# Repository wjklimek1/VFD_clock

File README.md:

# VFD_clock
Clock with VFD display based on STM32 MCU. Displays time, date and temperature.

As a display i used an old VFD tube IW-18 (IV-18). Device displays time (hours, minutes and seconds), date and temperature. Clock is based on STM32F103C8T6 microcontroller and it was programmed with HAL libraries. To boost voltage to required level I used popular SX1308 step-up IC.To power VFD display filament with alternating current i used L293d H-bridge with single transistor serving as simple NOT gate.

Schematic and PCB were designed using KiCad. You can find schematic in PDF format in PDFs folder of this repository.

Sensors used in the project:
RTC - DS3231 I2C real time clock

DS18B20 - 1-Wire temperature sensor (not utilized in software yet)
DHT11   - digital relative humidity sensor (not utilized in software yet)

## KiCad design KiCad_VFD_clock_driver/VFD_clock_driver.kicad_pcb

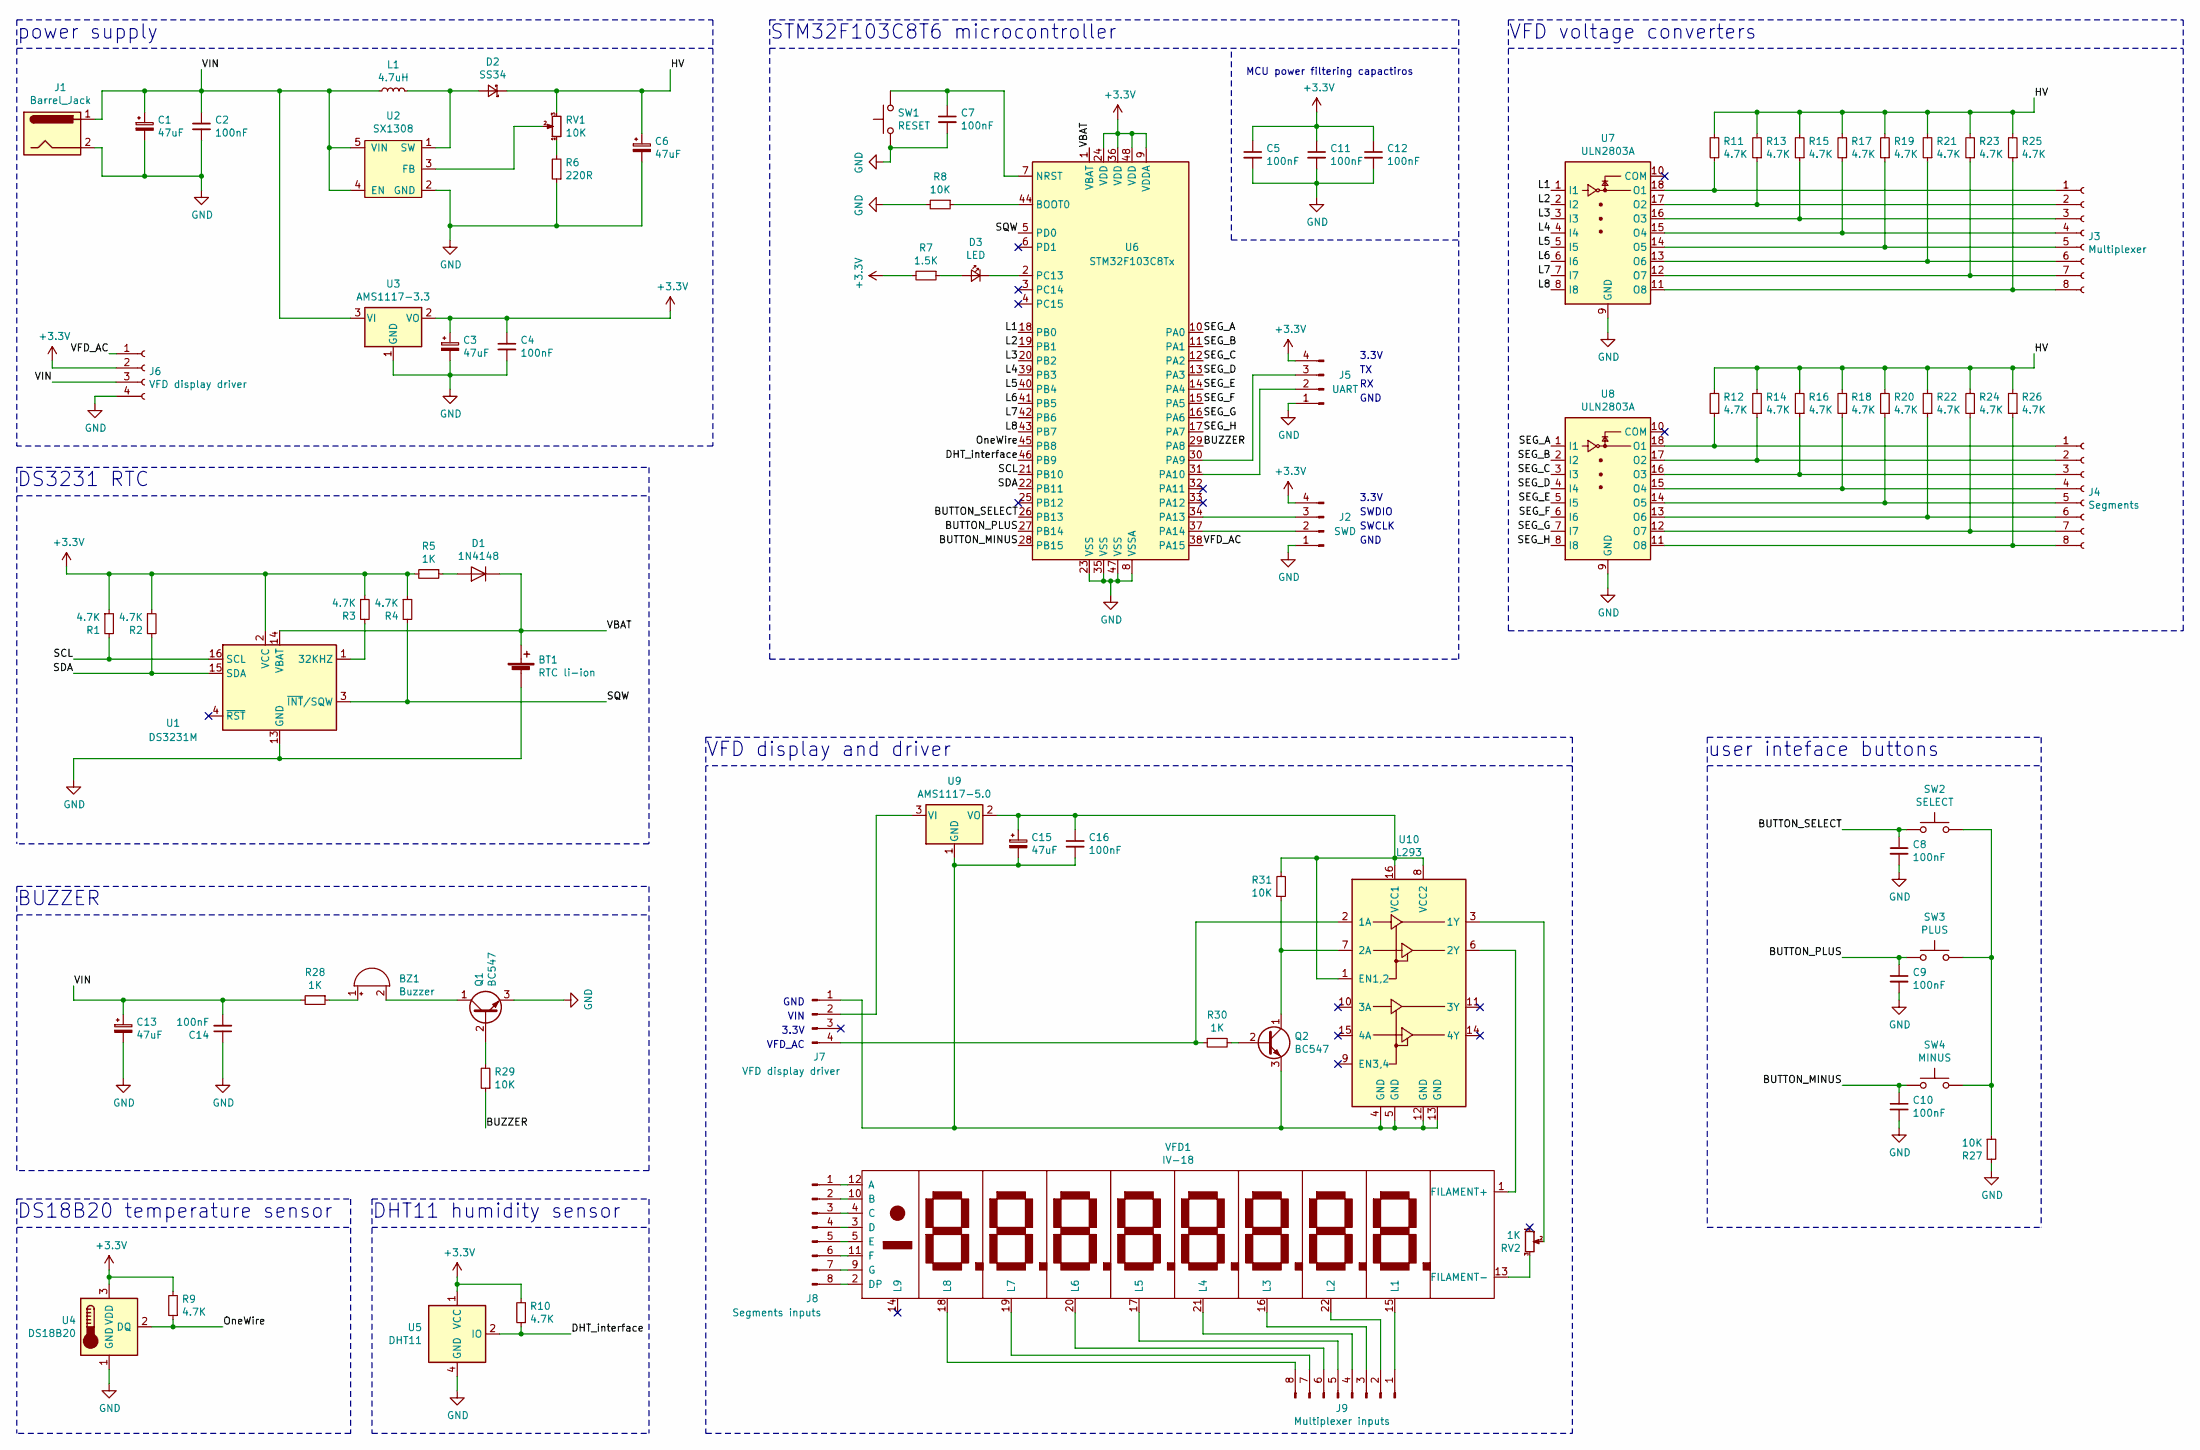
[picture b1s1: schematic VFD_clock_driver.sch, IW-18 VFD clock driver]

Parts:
BT1: RTC li-ion; BatteryHolder_Seiko_MS621F
BZ1: Buzzer; Buzzer_12x9.5RM7.6
C1, C3, C6, C13, C15: 47uF; CP_Elec_6.3x4.5
C2, C4, C5, C7, C8, C9, C10, C11, C12, C14, C16: 100nF; C_1206_3216Metric
D1: 1N4148; D_DO-35_SOD27_P7.62mm_Horizontal
D2: SS34; D_SMA
D3: LED; D_1206_3216Metric_Pad1.42x1.75mm_HandSolder
J1: Barrel_Jack; BarrelJack
J2: SWD; PinHeader_1x04_P2.54mm_Horizontal
J3: Multiplexer; PinSocket_1x08_P2.54mm_Vertical
J4: Segments; PinSocket_1x08_P2.54mm_Vertical
J5: UART; PinHeader_1x04_P2.54mm_Horizontal
J6: VFD display driver; PinSocket_1x04_P2.54mm_Vertical
J7: VFD display driver; PinHeader_1x04_P2.54mm_Vertical
J8: Segments inputs; PinHeader_1x08_P2.54mm_Vertical
J9: Multiplexer inputs; PinHeader_1x08_P2.54mm_Vertical
L1: 4.7uH; L_6.3x6.3_H3
Q1, Q2: BC547; TO-92_Inline
R1, R2, R3, R4, R9, R10, R11, R12, R13, R14, R15, R16, R17, R18, R19, R20, R21, R22, R23, R24, R25, R26: 4.7K; R_1206_3216Metric
R5, R28, R30: 1K; R_1206_3216Metric
R6: 220R; R_1206_3216Metric
R7: 1.5K; R_1206_3216Metric
R8, R27, R29, R31: 10K; R_1206_3216Metric
RV1: 10K; Potentiometer_Bourns_3296W_Vertical
RV2: 1K; Potentiometer_Piher_PT-6-V_Vertical_Hole
SW1: RESET; SW_SPST_TL3342
SW2: SELECT; SW_Tactile_SPST_Angled_PTS645Vx83-2LFS
SW3: PLUS; SW_Tactile_SPST_Angled_PTS645Vx83-2LFS
SW4: MINUS; SW_Tactile_SPST_Angled_PTS645Vx83-2LFS
U1: DS3231M; SOIC-16W_7.5x10.3mm_P1.27mm
U2: SX1308; SOT-23-6_Handsoldering
U3: AMS1117-3.3; SOT-223-3_TabPin2
U4: DS18B20; TO-92_Inline
U5: DHT11; Aosong_DHT11_5.5x12.0_P2.54mm
U6: STM32F103C8Tx; LQFP-48_7x7mm_P0.5mm
U7, U8: ULN2803A; SOP-18_7x12.5mm_P1.27mm
U9: AMS1117-5.0; SOT-223-3_TabPin2
U10: L293; DIP-16_W7.62mm
VFD1: IV-18

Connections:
+3V3: C3.1, C4.1, C5.1, C11.1, C12.1, J2.4, J5.4, J6.2, R1.1, R2.1, R3.1, R4.1, R5.2, R7.2, R9.2, R10.2, U1.2 (VCC), U3.2 (VO), U4.3 (VDD), U5.1 (VCC), U6.9 (VDDA), U6.24 (VDD), U6.36 (VDD), U6.48 (VDD)
/BUTTON_MINUS: C10.1, SW4.1, U6.28 (PB15)
/BUTTON_PLUS: C9.1, SW3.1, U6.27 (PB14)
/BUTTON_SELECT: C8.1, SW2.1, U6.26 (PB13)
/BUZZER: R29.1, U6.29 (PA8)
/DHT_interface: R10.1, U5.2 (IO), U6.46 (PB9)
/HV: C6.1, D2.1 (K), R11.2, R12.2, R13.2, R14.2, R15.2, R16.2, R17.2, R18.2, R19.2, R20.2, R21.2, R22.2, R23.2, R24.2, R25.2, R26.2, RV1.3
/L1: U6.18 (PB0), U7.1 (I1)
/L2: U6.19 (PB1), U7.2 (I2)
/L3: U6.20 (PB2), U7.3 (I3)
/L4: U6.39 (PB3), U7.4 (I4)
/L5: U6.40 (PB4), U7.5 (I5)
/L6: U6.41 (PB5), U7.6 (I6)
/L7: U6.42 (PB6), U7.7 (I7)
/L8: U6.43 (PB7), U7.8 (I8)
/OneWire: R9.1, U4.2 (DQ), U6.45 (PB8)
/SCL: R1.2, U1.16 (SCL), U6.21 (PB10)
/SDA: R2.2, U1.15 (SDA), U6.22 (PB11)
/SEG_A: U6.10 (PA0), U8.1 (I1)
/SEG_B: U6.11 (PA1), U8.2 (I2)
/SEG_C: U6.12 (PA2), U8.3 (I3)
/SEG_D: U6.13 (PA3), U8.4 (I4)
/SEG_E: U6.14 (PA4), U8.5 (I5)
/SEG_F: U6.15 (PA5), U8.6 (I6)
/SEG_G: U6.16 (PA6), U8.7 (I7)
/SEG_H: U6.17 (PA7), U8.8 (I8)
/SQW: R4.2, U1.3 (~INT~/SQW), U6.5 (PD0)
/VBAT: BT1.1 (+), D1.1 (K), U1.14 (VBAT), U6.1 (VBAT)
/VFD_AC: J6.1, U6.38 (PA15)
/VIN: C1.1, C2.1, C13.1, C14.2, J1.1, J6.3, L1.1, R28.2, U2.4 (EN), U2.5 (VIN), U3.3 (VI)
GND: BT1.2 (-), C1.2, C2.2, C3.2, C4.2, C5.2, C6.2, C7.2, C8.2, C9.2, C10.2, C11.2, C12.2, C13.2, C14.1, J1.2, J2.1, J5.1, J6.4, Q1.3 (E), R6.1, R8.2, R27.2, SW1.1, U1.5 (GND), U1.6 (GND), U1.7 (GND), U1.8 (GND), U1.9 (GND), U1.10 (GND), U1.11 (GND), U1.12 (GND), U1.13 (GND), U2.2 (GND), U3.1 (GND), U4.1 (GND), U5.4 (GND), U6.8 (VSSA), U6.23 (VSS), U6.35 (VSS), U6.47 (VSS), U7.9 (GND), U8.9 (GND)
unnamed: BZ1.1 (-), R28.1
unnamed: BZ1.2 (+), Q1.1 (C)
unnamed: C7.1, SW1.2, U6.7 (NRST)
unnamed: C15.1, C16.1, R31.2, U9.2 (VO), U10.1 (EN1,2), U10.8 (VCC2), U10.16 (VCC1)
unnamed: C15.2, C16.2, J7.1, Q2.3 (E), U9.1 (GND), U10.4 (GND), U10.5 (GND), U10.12 (GND), U10.13 (GND)
unnamed: D1.2 (A), R5.1
unnamed: D2.2 (A), L1.2, U2.1 (SW)
unnamed: D3.1 (K), U6.2 (PC13)
unnamed: D3.2 (A), R7.1
unnamed: J2.2, U6.37 (PA14)
unnamed: J2.3, U6.34 (PA13)
unnamed: J3.1, R11.1, U7.18 (O1)
unnamed: J3.2, R13.1, U7.17 (O2)
unnamed: J3.3, R15.1, U7.16 (O3)
unnamed: J3.4, R17.1, U7.15 (O4)
unnamed: J3.5, R19.1, U7.14 (O5)
unnamed: J3.6, R21.1, U7.13 (O6)
unnamed: J3.7, R23.1, U7.12 (O7)
unnamed: J3.8, R25.1, U7.11 (O8)
unnamed: J4.1, R12.1, U8.18 (O1)
unnamed: J4.2, R14.1, U8.17 (O2)
unnamed: J4.3, R16.1, U8.16 (O3)
unnamed: J4.4, R18.1, U8.15 (O4)
unnamed: J4.5, R20.1, U8.14 (O5)
unnamed: J4.6, R22.1, U8.13 (O6)
unnamed: J4.7, R24.1, U8.12 (O7)
unnamed: J4.8, R26.1, U8.11 (O8)
unnamed: J5.2, U6.31 (PA10)
unnamed: J5.3, U6.30 (PA9)
unnamed: J7.2, U9.3 (VI)
unnamed: J7.4, R30.1, U10.2 (1A)
unnamed: J8.1, VFD1.12 (A)
unnamed: J8.2, VFD1.10 (B)
unnamed: J8.3, VFD1.4 (C)
unnamed: J8.4, VFD1.3 (D)
unnamed: J8.5, VFD1.5 (E)
unnamed: J8.6, VFD1.11 (F)
unnamed: J8.7, VFD1.9 (G)
unnamed: J8.8, VFD1.2 (DP)
unnamed: J9.1, VFD1.15 (L1)
unnamed: J9.2, VFD1.22 (L2)
unnamed: J9.3, VFD1.16 (L3)
unnamed: J9.4, VFD1.21 (L4)
unnamed: J9.5, VFD1.17 (L5)
unnamed: J9.6, VFD1.20 (L6)
unnamed: J9.7, VFD1.19 (L7)
unnamed: J9.8, VFD1.18 (L8)
unnamed: Q1.2 (B), R29.2
unnamed: Q2.1 (C), R31.1, U10.7 (2A)
unnamed: Q2.2 (B), R30.2
unnamed: R3.2, U1.1 (32KHZ)
unnamed: R6.2, RV1.1
unnamed: R8.1, U6.44 (BOOT0)
unnamed: R27.1, SW2.2, SW3.2, SW4.2
unnamed: RV1.2, U2.3 (FB)
unnamed: RV2.2, U10.3 (1Y)
unnamed: RV2.3, VFD1.13 (FILAMENT-)
unnamed: U10.6 (2Y), VFD1.1 (FILAMENT+)

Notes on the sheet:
3.3V
SWDIO
SWCLK
GND
DS3231 RTC
power supply
DS18B20 temperature sensor
VFD voltage converters
user inteface buttons
DHT11 humidity sensor
STM32F103C8T6 microcontroller
MCU power filtering capactiros
BUZZER
VIN
VFD_AC
VFD display and driver

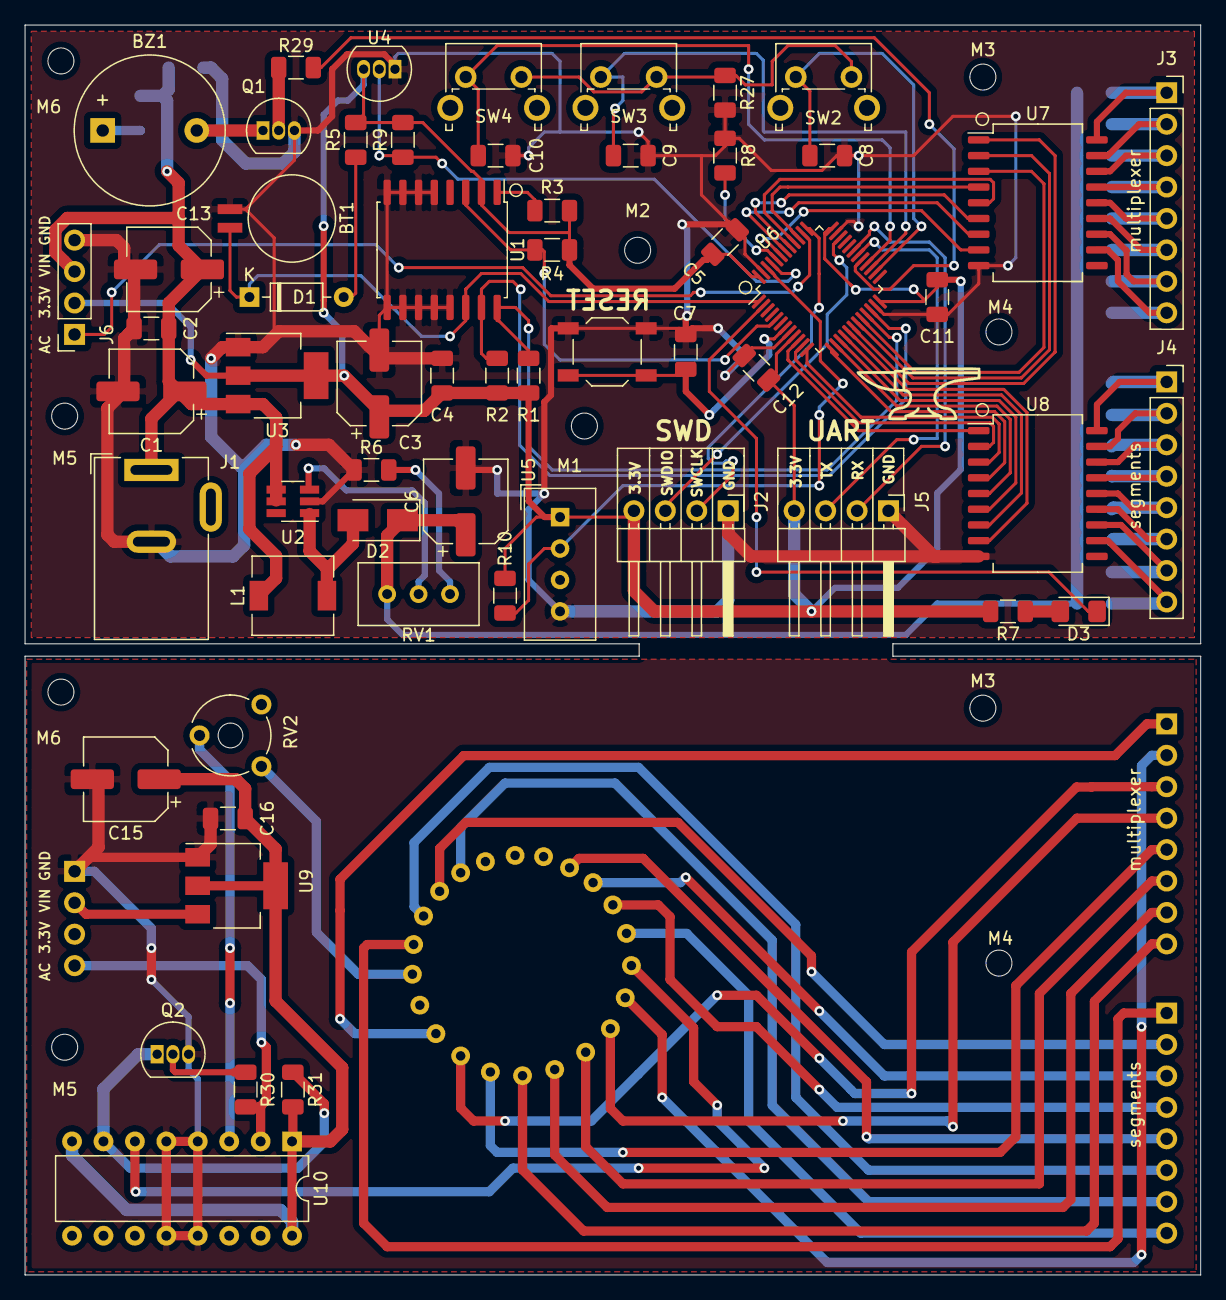
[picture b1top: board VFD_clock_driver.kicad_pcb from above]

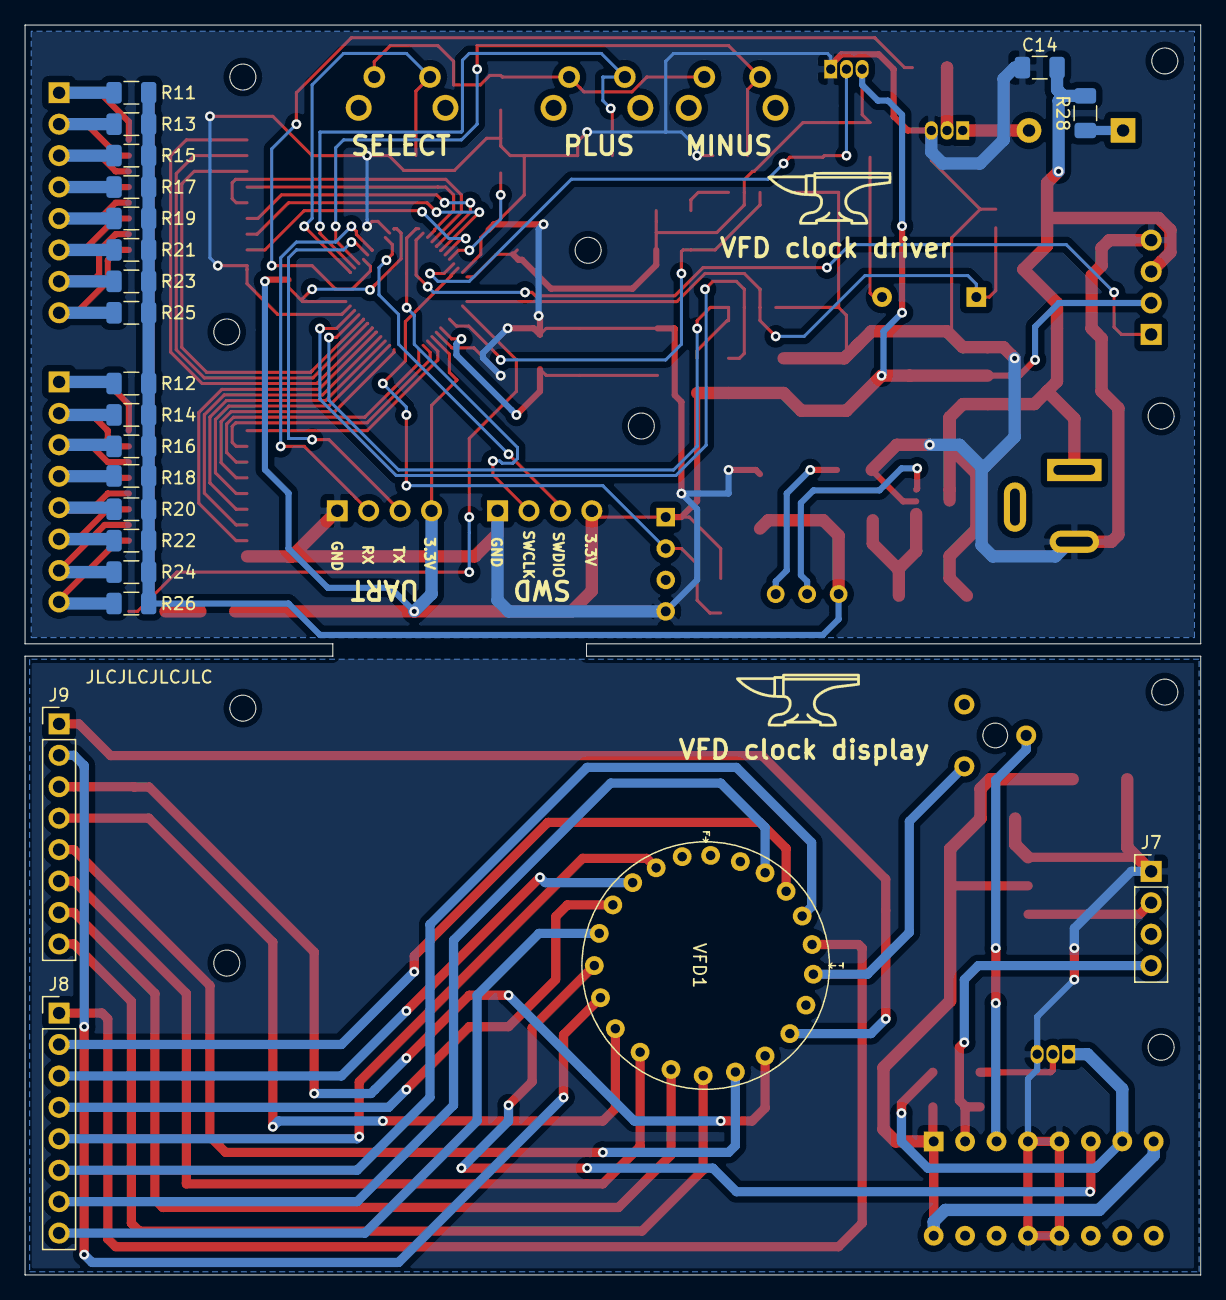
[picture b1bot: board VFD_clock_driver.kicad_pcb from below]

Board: 2 copper layers, 95.0 x 101.0 mm, 91 parts (22 on the bottom side), 89 nets.

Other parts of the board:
M1, M2, M3, M3#2, M4, M4#2, M5, M5#2, M6, M6#2: MountingHole_2.1mm

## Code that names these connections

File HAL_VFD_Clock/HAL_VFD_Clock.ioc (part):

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Mcu.Name=STM32F103C(8-B)Tx
Mcu.Package=LQFP48
Mcu.UserName=STM32F103C8Tx
PA0-WKUP.GPIOParameters=GPIO_Label
PA0-WKUP.GPIO_Label=SEG_A
PA0-WKUP.Signal=GPIO_Output
PA1.GPIOParameters=GPIO_Label
PA1.GPIO_Label=SEG_B
PA1.Signal=GPIO_Output
PA10.Mode=Asynchronous
PA10.Signal=USART1_RX
PA13.Mode=Serial_Wire
PA13.Signal=SYS_JTMS-SWDIO
PA14.Mode=Serial_Wire
PA14.Signal=SYS_JTCK-SWCLK
PA15.GPIOParameters=GPIO_Label
PA15.GPIO_Label=VFD_AC
PA15.Signal=S_TIM2_CH1_ETR
PA2.GPIOParameters=GPIO_Label
PA2.GPIO_Label=SEG_C
PA2.Signal=GPIO_Output
PA3.GPIOParameters=GPIO_Label
PA3.GPIO_Label=SEG_D
PA3.Signal=GPIO_Output
PA4.GPIOParameters=GPIO_Label
PA4.GPIO_Label=SEG_E
PA4.Signal=GPIO_Output
PA5.GPIOParameters=GPIO_Label
PA5.GPIO_Label=SEG_F
PA5.Signal=GPIO_Output
PA6.GPIOParameters=GPIO_Label
PA6.GPIO_Label=SEG_G
PA6.Signal=GPIO_Output
PA7.GPIOParameters=GPIO_Label
PA7.GPIO_Label=SEG_H
PA7.Signal=GPIO_Output
PA8.GPIOParameters=GPIO_Label
PA8.GPIO_Label=BUZZER
PA8.Signal=S_TIM1_CH1
PA9.Mode=Asynchronous
PA9.Signal=USART1_TX
PB0.GPIOParameters=GPIO_Label
PB0.GPIO_Label=L1
PB0.Signal=GPIO_Output
PB1.GPIOParameters=GPIO_Label
PB1.GPIO_Label=L2
PB1.Signal=GPIO_Output
PB10.Mode=I2C
PB10.Signal=I2C2_SCL
PB11.Mode=I2C
PB11.Signal=I2C2_SDA
PB13.GPIOParameters=GPIO_Label
PB13.GPIO_Label=BUTTON_SELECT
PB13.Signal=GPXTI13
PB14.GPIOParameters=GPIO_Label
PB14.GPIO_Label=BUTTON_PLUS
PB14.Signal=GPXTI14
PB15.GPIOParameters=GPIO_Label
PB15.GPIO_Label=BUTTON_MINUS
PB15.Signal=GPXTI15
PB2.GPIOParameters=GPIO_Label
PB2.GPIO_Label=L3
PB2.Signal=GPIO_Output
PB3.GPIOParameters=GPIO_Label
PB3.GPIO_Label=L4
PB3.Signal=GPIO_Output
PB4.GPIOParameters=GPIO_Label
PB4.GPIO_Label=L5
PB4.Signal=GPIO_Output
PB5.GPIOParameters=GPIO_Label
PB5.GPIO_Label=L6
PB5.Signal=GPIO_Output
PB6.GPIOParameters=GPIO_Label
PB6.GPIO_Label=L7
PB6.Signal=GPIO_Output
PB7.GPIOParameters=GPIO_Label
PB7.GPIO_Label=L8
PB7.Signal=GPIO_Output
PB8.GPIOParameters=GPIO_Label
PB8.GPIO_Label=DHT_interface
PB8.Signal=GPIO_Output
PB9.GPIOParameters=GPIO_Label
PB9.GPIO_Label=OneWire
PB9.Signal=GPIO_Output
PC13-TAMPER-RTC.GPIOParameters=GPIO_Label
PC13-TAMPER-RTC.GPIO_Label=LED
PC13-TAMPER-RTC.Signal=GPIO_Output
PD0-OSC_IN.GPIOParameters=GPIO_Label
PD0-OSC_IN.GPIO_Label=SQW
PD0-OSC_IN.Signal=GPXTI0
RCC.SYSCLKFreq_VALUE=64000000
RCC.SYSCLKSource=RCC_SYSCLKSOURCE_PLLCLK
board=custom

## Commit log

2020-07-14 Initial driver schematic
    + initial driver schematic
    + added project description to readme.md
    + added .gitignore
2020-11-17 Final driver schematic
    Final driver PCB schematic
2020-11-17 Buzzer and additional inputs
    + added buzzer with circuitry
    + SQW and UART connected to MCU
2020-11-19 Power supply section in PCB
2020-11-19 Final PCB routing
    + updated gitignore with some unnecessary KiCad files
    + final component placement on BCB
    + final routing on PCB
2020-11-19 Silkscreen and planes on PCB
    + final silkscreen on PCB
    + small routing and component location tweaks
    + GND planes on PCB
2020-11-19 VFD tube power connector on BCB
2020-11-23 External PCB for VFD tube and H-brigde
    + additional PCB for VFD tube with H-bridge
2020-11-24 Mounting holes on tube PCB
    + added mounting holed on tube PCB, new holes are aligned with old ones in driver PCB
    + fixed misplaced UART and SWD connectors descriptions on silkscreen
2020-12-31 CubeIDE project with peripherials initialization
    + added CubeIDE project with peripherials initialization in Cube
2021-01-01 Changes in footprints, changed VCC pin in SX1308
    + changed polarized capacitors footprints to biiger ones
    + changed SX1308 footprint to 6 legged version
    + changed logic VCC for L293 from 3.3V to 5V
2021-01-01 VFD display multiplexing
    + added multiplexing on TIM3 timer interrupt running with 1kHz frequency
    + added bit masks for various characters
    + migrtion to new CubeIDE version 1.5.1
2021-01-02 Displaying characters from a string
    + added function that can display characters from string
    + modified .gitignore and readme.md
2021-01-14 Separated .h and .c for display functions
    + separated header and source for display functions
    + added doxygen comments for display functions
    + added DS3231 RTC library
    + removed CubeMX comments from main.c
2021-01-14 Buttons EXTI callbacks, date and time displaying
    + implemented buttons EXTI Callback
    + implemented functions displaying date and time
2021-01-14 Time setting with buttons
    + setting time with flags, state machine and watchdog
    + blinking mask used to blink selected displays in multiplexer sequence
2021-01-14 Date setting with buttons
    + setting date in a way similar to setting time
    - function doesn't check number of days in given month what can lead to errors in saving time to RTC
2021-01-14 Changes in README and PDF schematic
    + added schematic in PDF format
    + changes in readme.md
2021-01-14 Images of real device in readme
2021-02-15 Clamp day range to number of days in current month
    + added function that checks number of days in current month and year
    + number of days in menu is clamped to correct number of days in current month and year
    + added some comments to function selecting time
    + when month gets decremented below 1 is changed for 12 instead of freezing
2021-02-16 Internal temperature display at startup
    + displaying internal circuit temperature from RTC at startup
    + fixed leading zeros flashing in hours and days
2021-02-18 Function prototypes in main.c and multiplexer optimization
    + added function prototypes in main.c file and moved main() to top
    + optimization and comments in MultiplexerSequence()
2021-04-07 Create .gitattributes to fix GitHub's broken language recognition
